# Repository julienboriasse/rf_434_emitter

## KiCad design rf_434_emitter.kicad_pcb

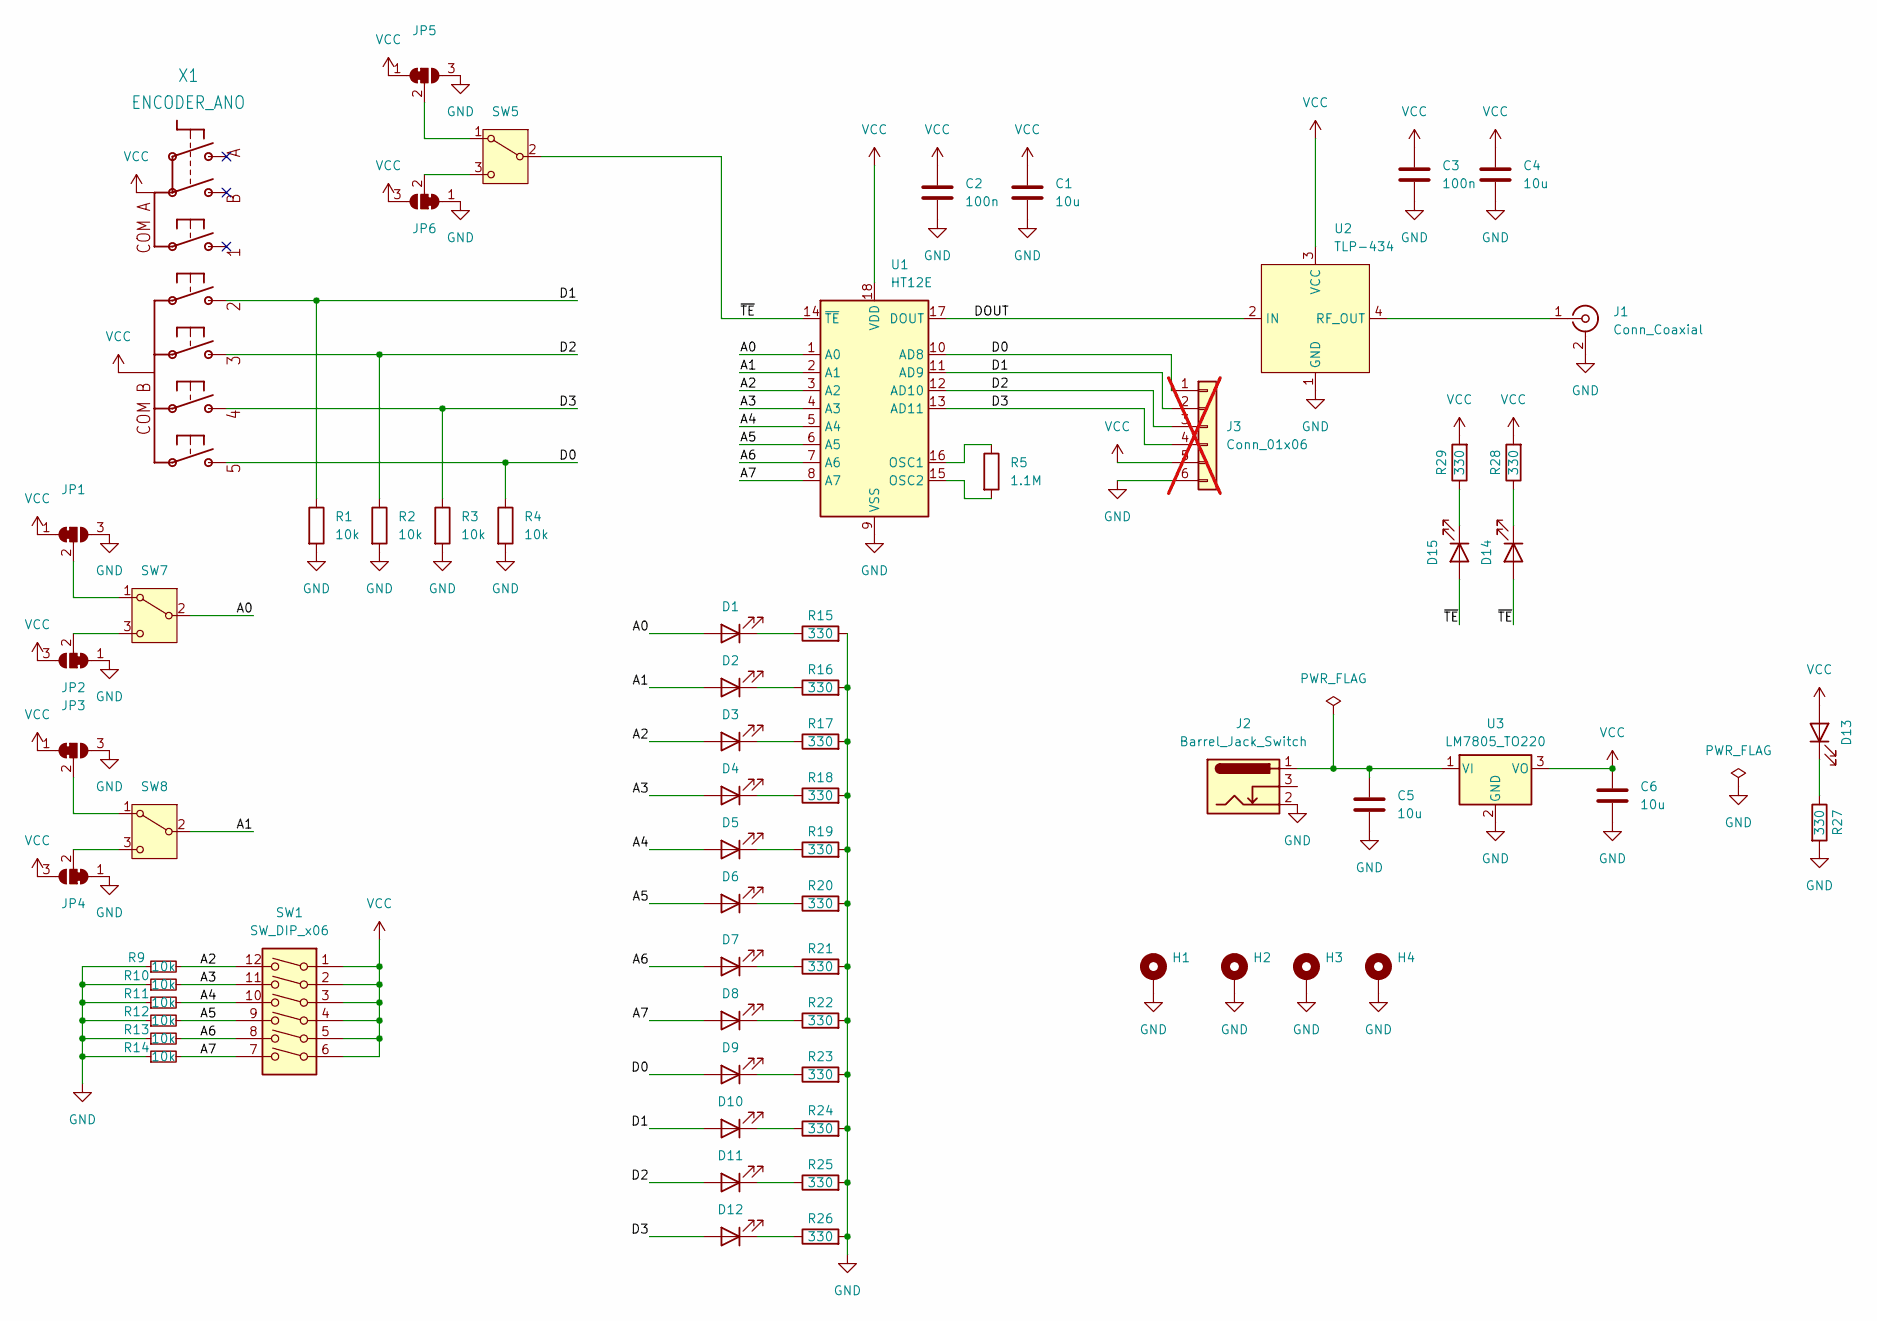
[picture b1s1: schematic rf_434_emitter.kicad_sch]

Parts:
C1, C4, C5, C6: 10u; C_0805_2012Metric_Pad1.18x1.45mm_HandSolder
C2, C3: 100n; C_0603_1608Metric_Pad1.08x0.95mm_HandSolder
D1, D2, D3, D4, D5, D6, D7, D8, D9, D10, D11, D12, D13, D14, D15: LED; LED_0603_1608Metric
H1, H2, H3, H4: MountingHole_Pad; MountingHole_4mm_Pad
J1: Conn_Coaxial; SMA_Amphenol_901-144_Vertical
J2: Barrel_Jack_Switch; BarrelJack_Kycon_KLDX-0202-xC_Horizontal
J3: Conn_01x06; PinHeader_1x06_P2.54mm_Vertical; not fitted
JP1, JP2, JP3, JP4, JP5, JP6: SolderJumper_3_Bridged12; SolderJumper-3_P1.3mm_Bridged12_RoundedPad1.0x1.5mm_NumberL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
R1, R2, R3, R4, R9, R10, R11, R12, R13, R14: 10k; R_0603_1608Metric_Pad0.98x0.95mm_HandSolder
R5: 1.1M; R_0603_1608Metric_Pad0.98x0.95mm_HandSolder
R15, R16, R17, R18, R19, R20, R21, R22, R23, R24, R25, R26, R27, R28, R29: 330; R_0603_1608Metric_Pad0.98x0.95mm_HandSolder
SW1: SW_DIP_x06; SW_DIP_SPSTx06_Slide_9.78x17.42mm_W7.62mm_P2.54mm
SW5, SW7, SW8: SW_SPDT; EG1218
U1: HT12E; DIP-18_W7.62mm_Socket
U2: TLP-434; PinSocket_1x04_P2.54mm_Vertical
U3: LM7805_TO220; TO-220-3_Vertical
X1: ENCODER_ANO

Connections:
/A0: D1.2 (A), SW7.2 (B), U1.1 (A0)
/A1: D2.2 (A), SW8.2 (B), U1.2 (A1)
/A2: D3.2 (A), R9.2, SW1.12, U1.3 (A2)
/A3: D4.2 (A), R10.2, SW1.11, U1.4 (A3)
/A4: D5.2 (A), R11.2, SW1.10, U1.5 (A4)
/A5: D6.2 (A), R12.2, SW1.9, U1.6 (A5)
/A6: D7.2 (A), R13.2, SW1.8, U1.7 (A6)
/A7: D8.2 (A), R14.2, SW1.7, U1.8 (A7)
/D0: D9.2 (A), J3.1, R4.1, U1.10 (AD8), X1.S5
/D1: D10.2 (A), J3.2, R1.1, U1.11 (AD9), X1.S2
/D2: D11.2 (A), J3.3, R2.1, U1.12 (AD10), X1.S3
/D3: D12.2 (A), J3.4, R3.1, U1.13 (AD11), X1.S4
/DOUT: U1.17 (DOUT), U2.2 (IN)
/~TE: D14.2 (A), D15.2 (A), SW5.2 (B), U1.14 (~TE)
GND: C1.2, C2.2, C3.2, C4.2, C5.2, C6.2, H1.1, H2.1, H3.1, H4.1, J1.2 (Ext), J2.2, J3.6, JP1.3 (B), JP2.1 (A), JP3.3 (B), JP4.1 (A), JP5.3 (B), JP6.1 (A), R1.2, R2.2, R3.2, R4.2, R9.1, R10.1, R11.1, R12.1, R13.1, R14.1, R15.2, R16.2, R17.2, R18.2, R19.2, R20.2, R21.2, R22.2, R23.2, R24.2, R25.2, R26.2, R27.2, U1.9 (VSS), U2.1 (GND), U3.2 (GND)
unnamed: D1.1 (K), R15.1
unnamed: D2.1 (K), R16.1
unnamed: D3.1 (K), R17.1
unnamed: D4.1 (K), R18.1
unnamed: D5.1 (K), R19.1
unnamed: D6.1 (K), R20.1
unnamed: D7.1 (K), R21.1
unnamed: D8.1 (K), R22.1
unnamed: D9.1 (K), R23.1
unnamed: D10.1 (K), R24.1
unnamed: D11.1 (K), R25.1
unnamed: D12.1 (K), R26.1
unnamed: D13.1 (K), R27.1
unnamed: D14.1 (K), R28.1
unnamed: D15.1 (K), R29.1
unnamed: J1.1 (In), U2.4 (RF_OUT)
unnamed: JP1.2 (C), SW7.1 (A)
unnamed: JP2.2 (C), SW7.3 (C)
unnamed: JP3.2 (C), SW8.1 (A)
unnamed: JP4.2 (C), SW8.3 (C)
unnamed: JP5.2 (C), SW5.1 (A)
unnamed: JP6.2 (C), SW5.3 (C)
unnamed: R5.1, U1.16 (OSC1)
unnamed: R5.2, U1.15 (OSC2)
unnamed: C5.1, J2.1, U3.1 (VI)
VCC: C1.1, C2.1, C3.1, C4.1, C6.1, D13.2 (A), J3.5, JP1.1 (A), JP2.3 (B), JP3.1 (A), JP4.3 (B), JP5.1 (A), JP6.3 (B), R28.2, R29.2, SW1.1, SW1.2, SW1.3, SW1.4, SW1.5, SW1.6, U1.18 (VDD), U2.3 (VCC), U3.3 (VO), X1.COM_A (COMA), X1.COM_B

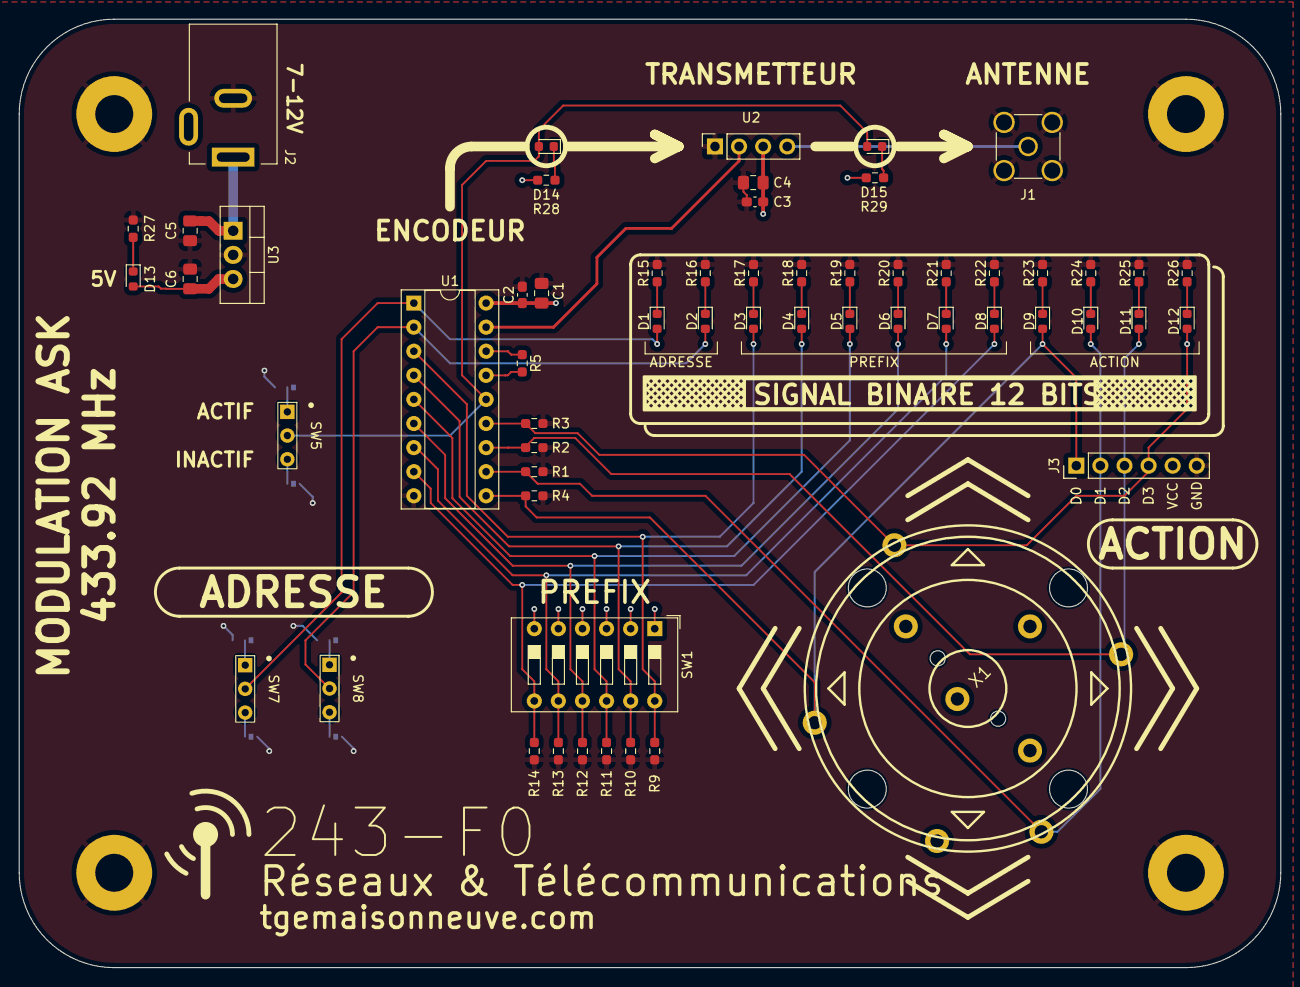
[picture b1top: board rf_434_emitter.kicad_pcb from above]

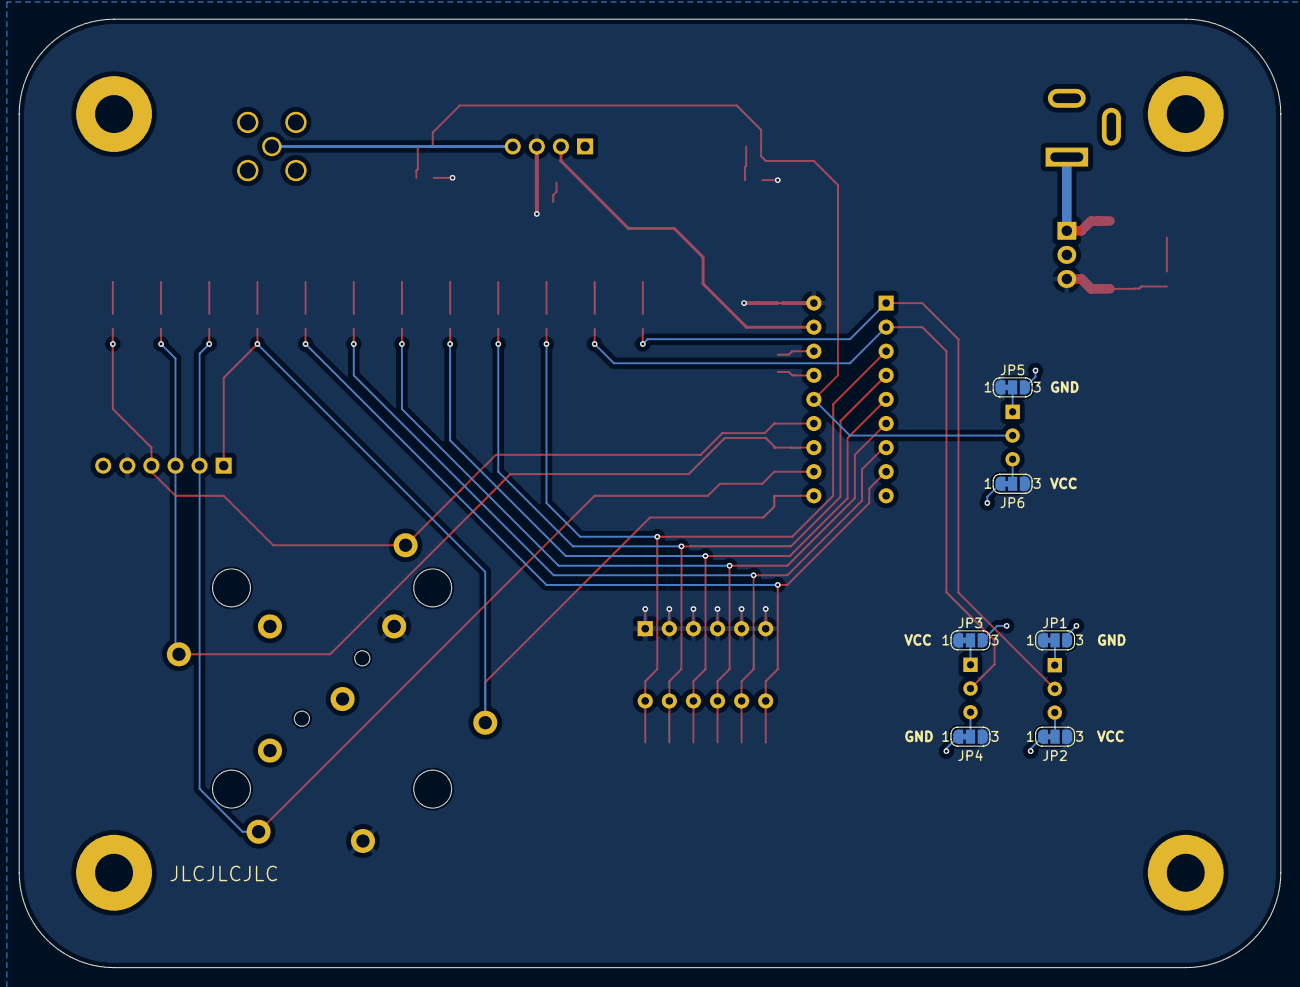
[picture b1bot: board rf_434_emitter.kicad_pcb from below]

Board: 2 copper layers, 133.0 x 100.0 mm, 68 parts (6 on the bottom side), 41 nets.

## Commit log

2024-10-15 DIP switch THT
2024-10-18 Remove receiver symbole
2024-10-18 Add D0-D3 connector
2024-10-24 Add 3D model Jack connector
2024-10-24 Inversion des LED \TE
2024-10-24 ATTENTION
    Symbole édité dans le schéma 02 pins à 18 pin
